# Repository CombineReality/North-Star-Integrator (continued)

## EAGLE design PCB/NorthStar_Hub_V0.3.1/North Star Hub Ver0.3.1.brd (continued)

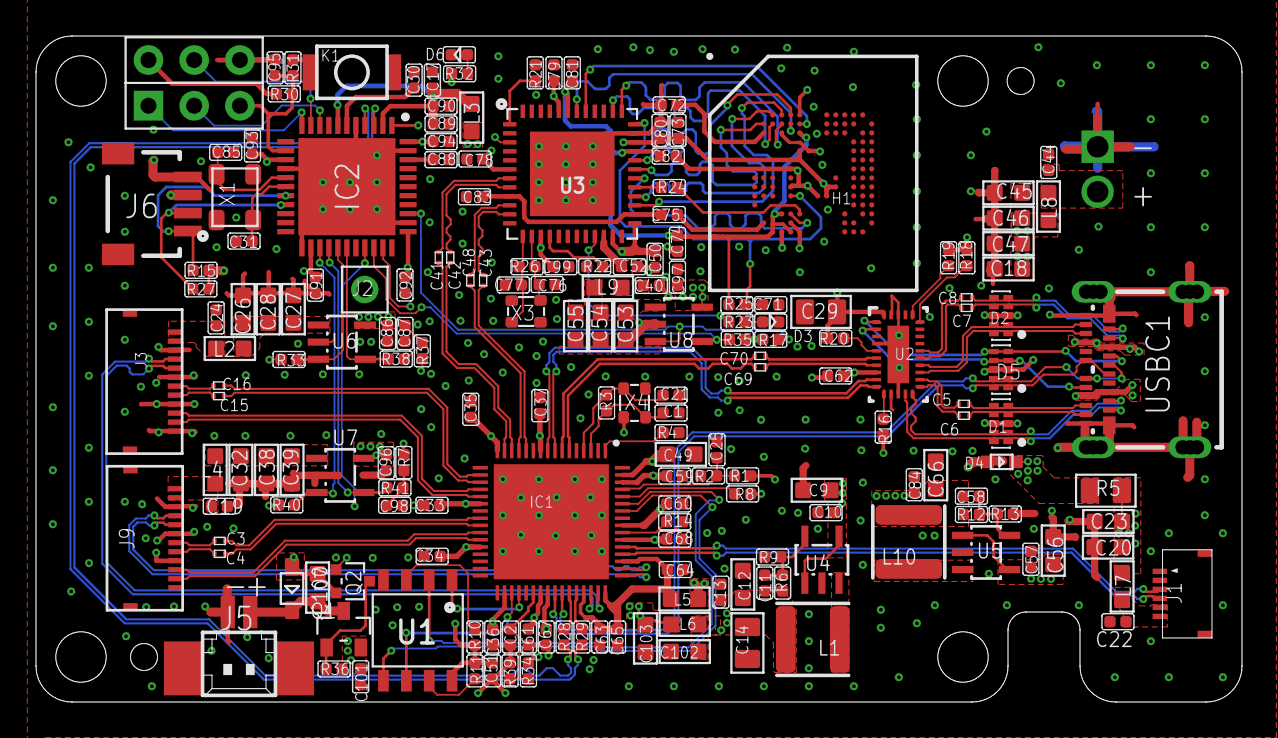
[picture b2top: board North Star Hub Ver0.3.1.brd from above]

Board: 4 copper layers, 67.0 x 37.0 mm, 187 parts (1 on the bottom side), 136 nets.

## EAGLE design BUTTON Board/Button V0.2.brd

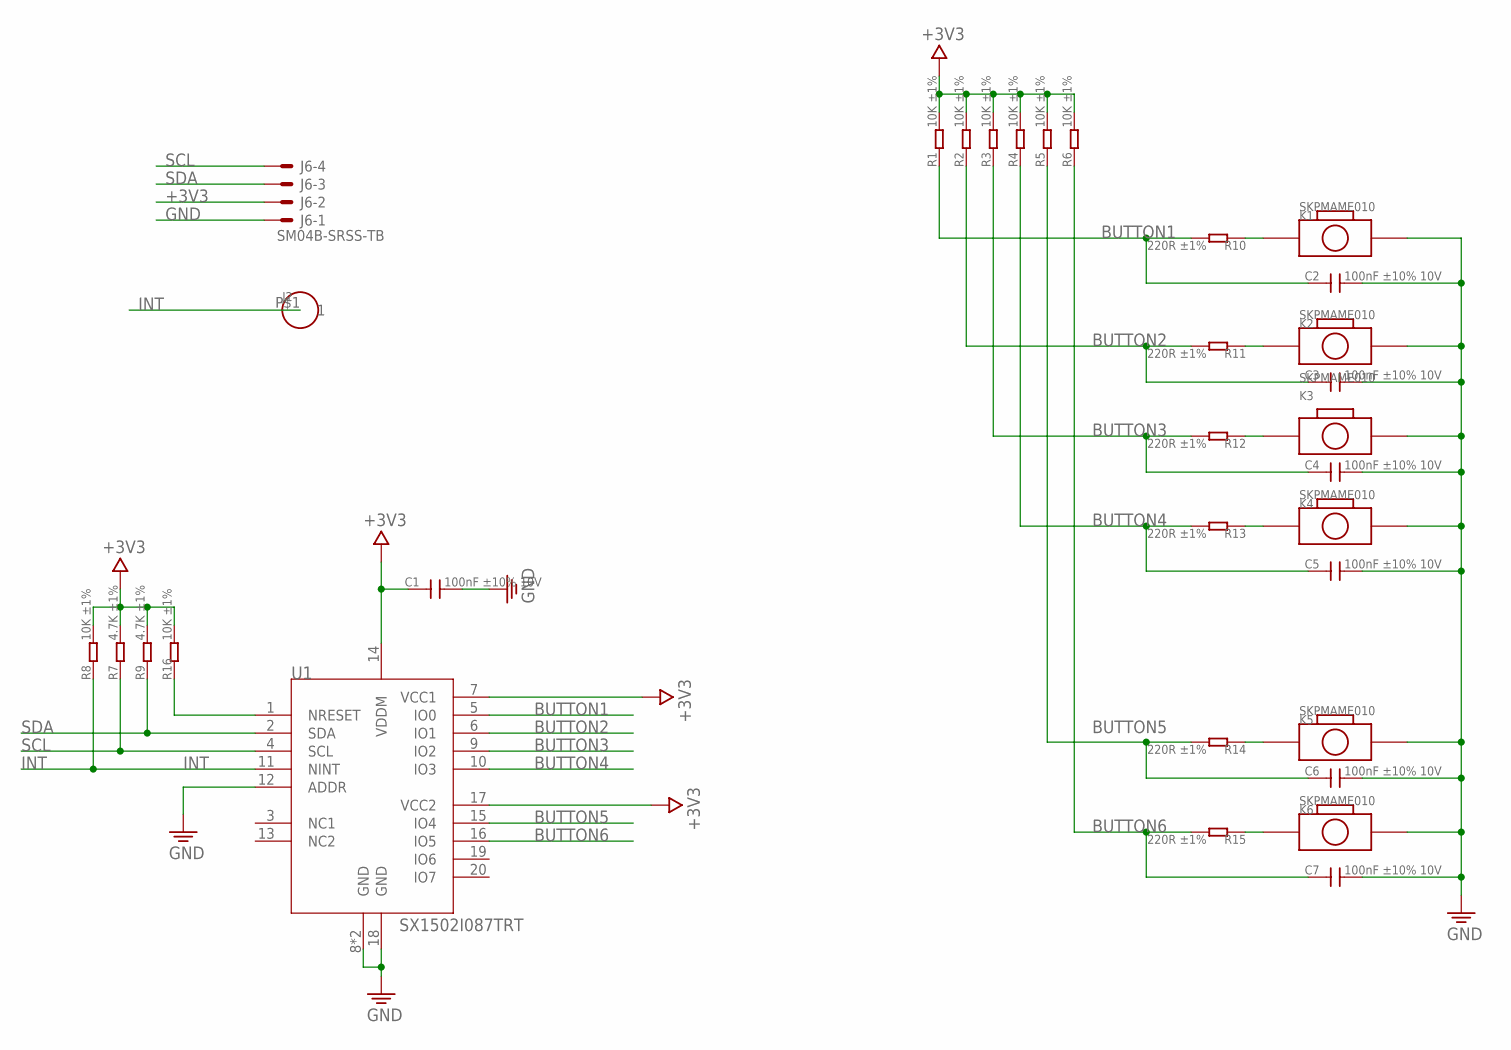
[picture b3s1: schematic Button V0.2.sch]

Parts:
C1, C2, C3, C4, C5, C6, C7: 100nF ±10% 10V; C0402
J2: HEADER-1P-32; 1P-60/32MIL
J6: SM04B-SRSS-TB
K1, K2, K3, K4, K5, K6: SKPMAME010
R1, R2, R3, R4, R5, R6, R8, R16: 10K ±1%; R0402
R7, R9: 4.7K ±1%; R0402
R10, R11, R12, R13, R14, R15: 220R ±1%; R0402
U1: SX1502I087TRT; QFN-20-3X3MM

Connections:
+3V3: C1.1, J6.2, R1.2, R2.2, R3.2, R4.2, R5.2, R6.2, R7.2, R8.2, R9.2, R16.2, U1.7 (VCC1), U1.14 (VDDM), U1.17 (VCC2)
BUTTON1: C2.1, R1.1, R10.2, U1.5 (IO0)
BUTTON2: C3.1, R2.1, R11.2, U1.6 (IO1)
BUTTON3: C4.1, R3.1, R12.2, U1.9 (IO2)
BUTTON4: C5.1, R4.1, R13.2, U1.10 (IO3)
BUTTON5: C6.1, R5.1, R14.2, U1.15 (IO4)
BUTTON6: C7.1, R6.1, R15.2, U1.16 (IO5)
GND: C1.2, C2.2, C3.2, C4.2, C5.2, C6.2, C7.2, J6.1, K1.2, K2.2, K3.2, K4.2, K5.2, K6.2, U1.8 (GND), U1.12 (ADDR), U1.18 (GND), U1.21 (GND)
INT: J2.P$1, R8.1, U1.11 (NINT)
unnamed: K1.1, R10.1
unnamed: K2.1, R11.1
unnamed: K3.1, R12.1
unnamed: K4.1, R13.1
unnamed: K5.1, R14.1
unnamed: K6.1, R15.1
unnamed: R16.1, U1.1 (NRESET)
SCL: J6.4, R7.1, U1.4 (SCL)
SDA: J6.3, R9.1, U1.2 (SDA)

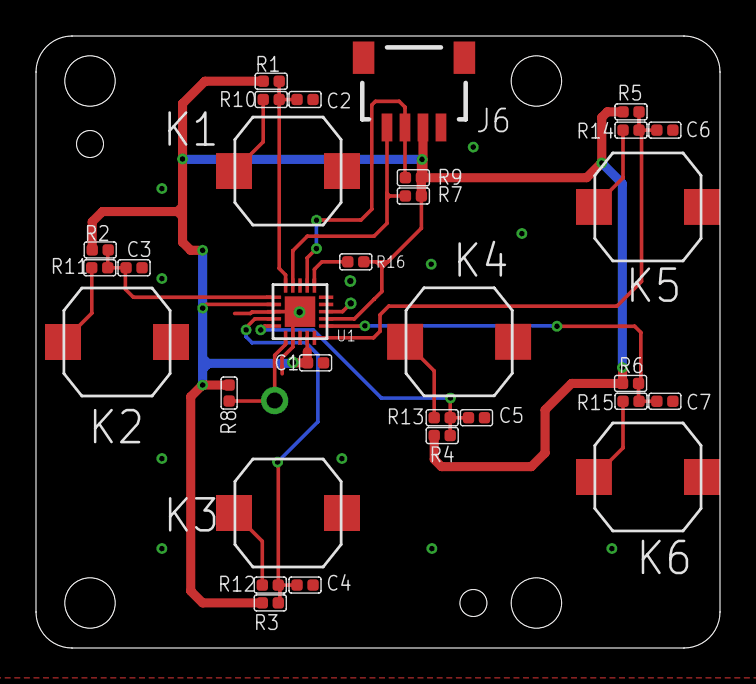
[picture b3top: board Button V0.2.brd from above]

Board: 2 copper layers, 38.0 x 34.0 mm, 32 parts (1 on the bottom side), 18 nets.

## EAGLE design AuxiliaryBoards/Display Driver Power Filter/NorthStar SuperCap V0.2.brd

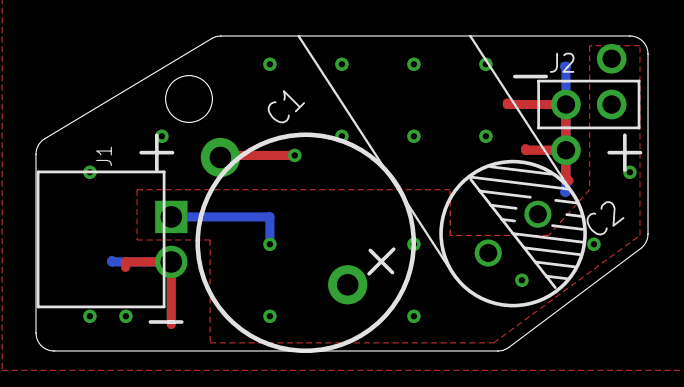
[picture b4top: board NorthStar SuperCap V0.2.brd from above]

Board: 2 copper layers, 34.0 x 17.5 mm, 4 parts (0 on the bottom side), 2 nets.

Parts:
C1: DCS5R5104; 11.5X5.5MM-P10
C2: 10YXF470MEFCT78X11.5; ELECTRO-8.0MM
J1: B2B-XH-A(LF)(SN); XH-02-90
J2: A2541HWV-2P; 2P-2.54-BOTTOM-ENTRY

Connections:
GND: C1.2, C2.-, J1.2, J2.2, J2.2-2
VBUS: C1.1, C2.+, J1.1, J2.1, J2.1-1

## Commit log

2020-08-24 Create LICENSE
2020-08-25 added the schematic as a pdf for each project
2020-09-15 firmware added
2020-09-15 removed file
2020-09-15 added files
2020-09-16 test
2020-09-16 file removal
2020-09-16 added firmware
2020-09-16 added Exmample Sketches
2020-09-16 added Example Sketches
2020-09-16 added IntegratorExampleSketches
2020-09-23 Update NorthStarHubTest.ino
    Corrected comments for left() and right() button functions as assigned for factory test protocol
2020-10-26 reassign INT to PE6
2020-10-30 repo re-structured
2021-02-20 Delete IntegratorExampleSketches directory
    Sketches can be found in the /firmware/ExampleSketches directory
2021-02-20 Update NorthStarButtons.ino
    added missing breaks to serial command char parser switch
2021-02-24 Create docs folder and readme
2021-03-11 Create NorthStarButtonsSR170.ino
    This stopps Port 1 from turning off in the portReset and portDisable functions; which interferes with the SR 170 (Rigel) connection.
2021-04-07 Update NorthStarButtons.ino
    Commented out serial passthrough toggle accidentally left in circle() button function.
2023-04-10 :sparkles: (ns-sketch) Add fan curve based on thermistor temperature
2023-04-10 :sparkles: (ns-sketch) Write PWM documentation and rename header file (case-sensitive on UNIX)
2023-04-10 :pencil: (ns-sketch) Add instructions for affixing thermistor.
2023-04-10 :pencil: (ns-sketch) Fix typo in usermod command
